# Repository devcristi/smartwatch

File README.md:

# Bare Metal STM-32 Nucleo Based SmartWatch# Bare Metal STM-32 Nucleo Based SmartWatch

## Project Overview## Project Overview

This project is a bare-metal implementation of a smartwatch using an AVR microcontroller (ATmega2560). The smartwatch is designed to operate at a low level, utilizing direct register manipulation and avoiding high-level abstractions. The entire project is written in C with modular architecture.This project is a bare-metal implementation of a smartwatch using the STM-32 Nucleo development board. The smartwatch is designed to operate at a low level, utilizing direct register manipulation and avoiding high-level abstractions. The project is written entirely in C.

## Features## Features

- **Real-Time Clock (RTC)**: DS3231 module for precise timekeeping with I2C interface- **Real-Time Clock (RTC)**: DS3231 module for precise timekeeping.

- **LCD Display**: GC9A01 compatible 16x2 LCD via I2C- **Motion Sensing**: MPU6050 sensor for accelerometer and gyroscope data.

- **Menu Navigation**: 3-mode menu system (Time, Temperature, Stopwatch)- **Heart Rate and SpO2 Monitoring**: MAX30102 sensor for health monitoring.

- **Stopwatch Functionality**: Start/Pause and Reset operations with centisecond precision- **Environmental Sensing**: BME280 sensor for temperature, humidity, and pressure measurements.

- **Temperature Monitoring**: Real-time temperature reading from DS3231 sensor- **Battery Management**: TP4056 module for battery charging and monitoring.

- **Button Control**: Three interrupt-driven buttons for navigation and control- **Display**: GC9A01 round LCD for user interface.

- **Timer-Based Scheduling**: TIMER1 for precise timing and interrupt handling

## Development Approach

## Hardware Components- **Bare-Metal Programming**: The project is implemented without an operating system, focusing on low-level programming.

1. **ATmega2560 Microcontroller**: Core processor- **Direct Register Access**: All peripherals are controlled through direct register manipulation, ensuring maximum control and efficiency.

2. **DS3231 RTC Module**: Real-time clock and temperature sensor (I2C @ 0x68)- **Low-Level Drivers**: Custom drivers are developed for each module to interface with the STM-32 microcontroller.

3. **LCD 16x2 Module**: Display with I2C backpack (I2C @ 0x27)

4. **Push Buttons**: ## Hardware Components

   - Button NEXT (PE4, INT4): Navigate menu forward1. **STM-32 Nucleo Board**: The core microcontroller platform.

   - Button PREV (PE5, INT5): Navigate menu backward  2. **DS3231 RTC Module**: Provides accurate timekeeping.

   - Button ACTION (PD2, INT2): Start/Pause/Reset stopwatch3. **MPU6050 Sensor**: Measures motion and orientation.

4. **MAX30102 Sensor**: Monitors heart rate and SpO2 levels.

## Project Structure5. **BME280 Sensor**: Captures environmental data such as temperature, humidity, and pressure.

```6. **TP4056 Module**: Manages battery charging.

smartwatch/7. **GC9A01 LCD**: Displays smartwatch data and user interface.

├── Core/

│   ├── Inc/                    # Header files## Goals

│   │   ├── main.h              # Main application header- Develop a fully functional smartwatch with essential features.

│   │   ├── i2c.h               # I2C/TWI interface- Implement all functionalities using bare-metal programming techniques.

│   │   ├── buttons.h           # Button handling- Optimize performance and power consumption through efficient low-level coding.

│   │   ├── timer.h             # Timer interrupt handling

│   │   └── stopwatch.h         # Stopwatch interface## Future Enhancements

│   └── Src/                    # Source files- Add additional sensors or modules for extended functionality.

│       ├── main.c              # Main application logic- Implement power-saving modes to extend battery life.

│       ├── i2c.c               # I2C driver implementation- Enhance the user interface with advanced graphics.

│       ├── buttons.c           # Button ISR and handling

│       ├── timer.c             # Timer ISR implementation## Getting Started

│       └── stopwatch.c         # Stopwatch logic1. Clone the repository.

├── Drivers/2. Set up the STM-32 Nucleo board with the required hardware components.

│   └── Custom/3. Compile the code using your preferred ARM compiler.

│       ├── Inc/4. Flash the firmware onto the STM-32 Nucleo board.

│       │   ├── lcd_i2c.h       # LCD I2C driver header5. Connect the hardware modules and power up the system.

│       │   └── ds3231.h        # DS3231 RTC driver header

│       └── Src/## License

│           ├── lcd_i2c.c       # LCD I2C driver implementationThis project is open-source and available under the MIT License.
│           └── ds3231.c        # DS3231 RTC driver implementation
└── README.md                   # This file
```

## Development Approach
- **Bare-Metal Programming**: No OS, direct hardware register access
- **Direct Register Manipulation**: Full control over microcontroller peripherals
- **Modular Architecture**: Separated concerns for easy maintenance and extension
- **ISR-Driven**: Interrupt Service Routines for button inputs and timing
- **I2C Communication**: Two-wire interface for RTC and LCD modules

## Functional Modes

### Mode 1: TIME Display
- Shows current time from DS3231 RTC
- Format: HH:MM:SS
- Hold PREV button (>1s) to reset clock to 00:00:00

### Mode 2: TEMPERATURE Display
- Shows current temperature from DS3231 sensor
- Format: XX.XX°C (with 0.25°C precision)

### Mode 3: STOPWATCH
- Start/Pause: Short press of ACTION button
- Reset: Long press (>1s) of ACTION button
- Format: MM:SS:CS (minutes:seconds:centiseconds)

## Building the Project

### Prerequisites
- ARM GCC compiler for AVR (avr-gcc)
- avrdude for flashing
- Make (optional, for automated builds)

### Compilation
```bash
avr-gcc -mmcu=atmega2560 -DF_CPU=16000000UL -O2 \
  Core/Src/*.c Drivers/Custom/Src/*.c \
  -o smartwatch.elf

avr-objcopy -O ihex smartwatch.elf smartwatch.hex
```

### Flashing
```bash
avrdude -p m2560 -c stk500v2 -P COM3 -b 115200 -U flash:w:smartwatch.hex:i
```

## Pin Configuration

| Function | Pin | AVR Port | Interrupt |
|----------|-----|----------|-----------|
| Button NEXT | PE4 | PORTE4 | INT4 |
| Button PREV | PE5 | PORTE5 | INT5 |
| Button ACTION | PD2 | PORTD2 | INT2 |
| I2C SDA | PD1 | PORTD1 | - |
| I2C SCL | PD0 | PORTD0 | - |

## I2C Configuration
- **Speed**: 100 kHz (TWBR = 72)
- **Devices**:
  - DS3231 RTC: Address 0x68
  - LCD Module: Address 0x27

## Timer Configuration
- **Timer1**: 16-bit CTC mode
- **Prescaler**: 256 (CS12 = 1)
- **Compare Register**: 624 (generates 10ms interrupt at 16MHz)
- **Frequency**: 100 Hz system ticks

## Interrupt Service Routines
1. **INT4_vect**: NEXT button handler
2. **INT5_vect**: PREV button handler
3. **INT2_vect**: ACTION button handler
4. **TIMER1_COMPA_vect**: Timer compare interrupt for timing

## Key Features Implementation

### Debouncing
- 50ms software debounce on button presses
- Prevents false triggers from mechanical contact bounce

### Time Management
- System ticks every 10ms (from TIMER1)
- Stopwatch counts in 10ms increments
- Button press timing for long-press detection

### I2C Communication
- Blocking I2C transfers (appropriate for low-speed communication)
- Standard START/STOP conditions
- ACK/NACK handling for multi-byte reads

## Future Enhancements
- Add additional sensors (accelerometer MPU6050, heart rate MAX30102)
- Implement BME280 environmental sensor
- Add TP4056 battery charging management
- Power management and sleep modes
- More sophisticated menu system with settings
- Data logging capabilities

## Troubleshooting

### LCD Not Displaying
1. Check I2C address (0x27) with I2C scanner
2. Verify pull-up resistors on SDA/SCL lines
3. Check contrast adjustment on LCD module

### RTC Time Not Updating
1. Verify DS3231 I2C address (0x68)
2. Check if coin cell battery is installed
3. Ensure I2C communication is working

### Buttons Not Responding
1. Check pin configuration matches header defines
2. Verify pull-up resistors are present
3. Test with multimeter for continuity

## License
This project is open-source and available under the MIT License.

## Author
devcristi - Embedded Systems Development

## References
- AVR ATmega2560 Datasheet
- DS3231 RTC Datasheet
- I2C/TWI Communication Protocol

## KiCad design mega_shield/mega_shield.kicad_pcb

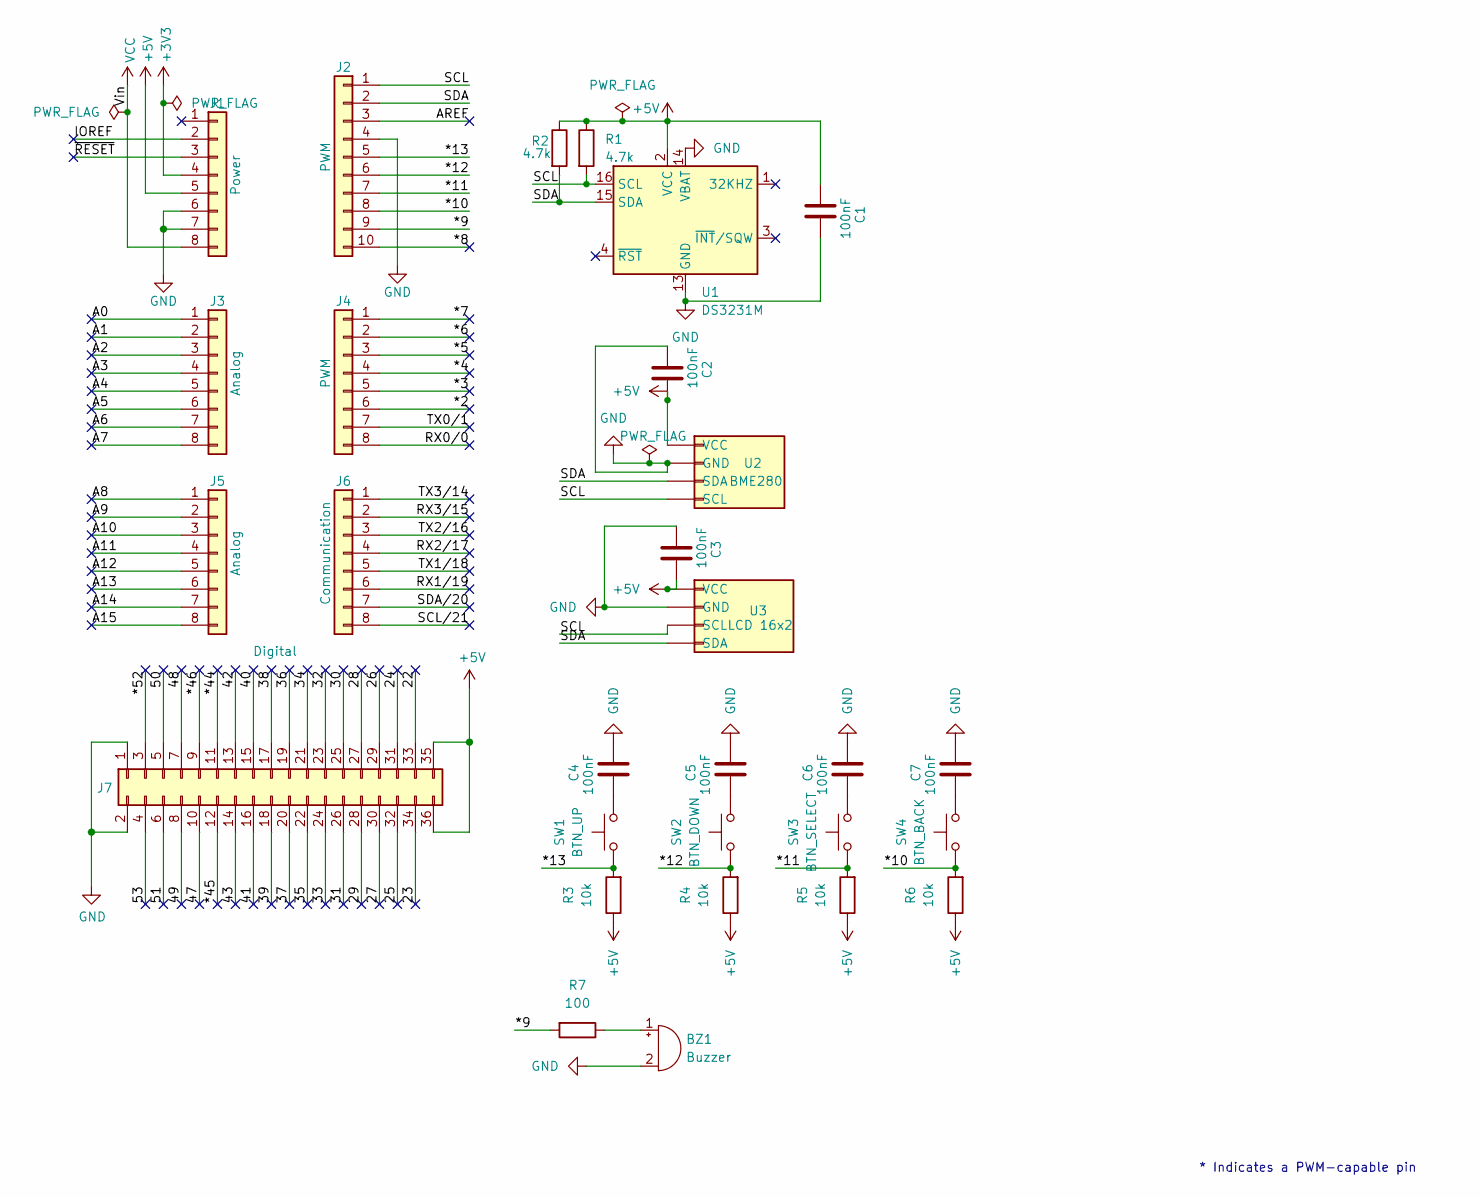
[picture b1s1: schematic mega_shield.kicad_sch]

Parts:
BZ1: Buzzer; Buzzer_12x9.5RM7.6
C1, C2, C3, C4, C5, C6, C7: 100nF; C_0805_2012Metric
J1: Power; PinHeader_1x08_P2.54mm_Vertical
J2: PWM; PinSocket_1x10_P2.54mm_Vertical
J3, J5: Analog; PinSocket_1x08_P2.54mm_Vertical
J4: PWM; PinSocket_1x08_P2.54mm_Vertical
J6: Communication; PinSocket_1x08_P2.54mm_Vertical
J7: Digital; PinSocket_2x18_P2.54mm_Vertical
R1, R2: 4.7k; R_0805_2012Metric
R3, R4, R5, R6: 10k; R_0805_2012Metric
R7: 100; R_0805_2012Metric
SW1: BTN_UP; SW_PUSH_6mm
SW2: BTN_DOWN; SW_PUSH_6mm
SW3: BTN_SELECT; SW_PUSH_6mm
SW4: BTN_BACK; SW_PUSH_6mm
U1: DS3231M; SOIC-16W_7.5x10.3mm_P1.27mm
U2: BME280; PinSocket_1x04_P2.54mm_Vertical
U3: LCD 16x2

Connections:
+3V3: J1.4
+5V: C1.1, C2.2, C3.2, J1.5, J7.35, J7.36, R1.1, R2.1, R3.1, R4.1, R5.1, R6.1, U1.2 (VCC), U2.1 (VCC), U3.1 (VCC)
/22: J7.33
/23: J7.34
/24: J7.31
/25: J7.32
/26: J7.29
/27: J7.30
/28: J7.27
/29: J7.28
/30: J7.25
/31: J7.26
/32: J7.23
/33: J7.24
/34: J7.21
/35: J7.22
/36: J7.19
/37: J7.20
/38: J7.17
/39: J7.18
/40: J7.15
/41: J7.16
/42: J7.13
/43: J7.14
/47: J7.10
/48: J7.7
/49: J7.8
/50: J7.5
/51: J7.6
/53: J7.4
/*2: J4.6
/*3: J4.5
/*4: J4.4
/*5: J4.3
/*6: J4.2
/*7: J4.1
/*8: J2.10
/*9: J2.9, R7.2
/*10: J2.8, R6.2, SW4.1
/*11: J2.7, R5.2, SW3.1
/*12: J2.6, R4.2, SW2.1
/*13: J2.5, R3.2, SW1.1
/*44: J7.11
/*45: J7.12
/*46: J7.9
/*52: J7.3
/A0: J3.1
/A1: J3.2
/A2: J3.3
/A3: J3.4
/A4: J3.5
/A5: J3.6
/A6: J3.7
/A7: J3.8
/A8: J5.1
/A9: J5.2
/A10: J5.3
/A11: J5.4
/A12: J5.5
/A13: J5.6
/A14: J5.7
/A15: J5.8
/AREF: J2.3
/IOREF: J1.2
/RX0/0: J4.8
/RX1/19: J6.6
/RX2/17: J6.4
/RX3/15: J6.2
/SCL/21: J6.8
/SDA/20: J6.7
/TX0/1: J4.7
/TX1/18: J6.5
/TX2/16: J6.3
/TX3/14: J6.1
/~RESET: J1.3
GND: BZ1.2 (-), C1.2, C2.1, C3.1, C4.2, C5.2, C6.2, C7.2, J1.6, J1.7, J2.4, J7.1, J7.2, U1.5 (GND), U1.6 (GND), U1.7 (GND), U1.8 (GND), U1.9 (GND), U1.10 (GND), U1.11 (GND), U1.12 (GND), U1.13 (GND), U1.14 (VBAT), U2.2 (GND), U3.2 (GND)
unnamed: BZ1.1 (+), R7.1
unnamed: C4.1, SW1.2
unnamed: C5.1, SW2.2
unnamed: C6.1, SW3.2
unnamed: C7.1, SW4.2
VCC: J1.8

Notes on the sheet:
* Indicates a PWM-capable pin

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
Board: 2 copper layers, 34 parts (0 on the bottom side), 13 nets, no tracks yet.

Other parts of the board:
MH1, MH2, MH3, MH4, MH5, MH6: MountingHole_3.2mm

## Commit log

2025-10-10 created readme
2025-10-10 project structure
2025-10-25 Organized project structure with modular drivers and core files
2025-10-25 Add comprehensive README documentation
2025-11-06 ✅ Initial commit - Schematic complete
